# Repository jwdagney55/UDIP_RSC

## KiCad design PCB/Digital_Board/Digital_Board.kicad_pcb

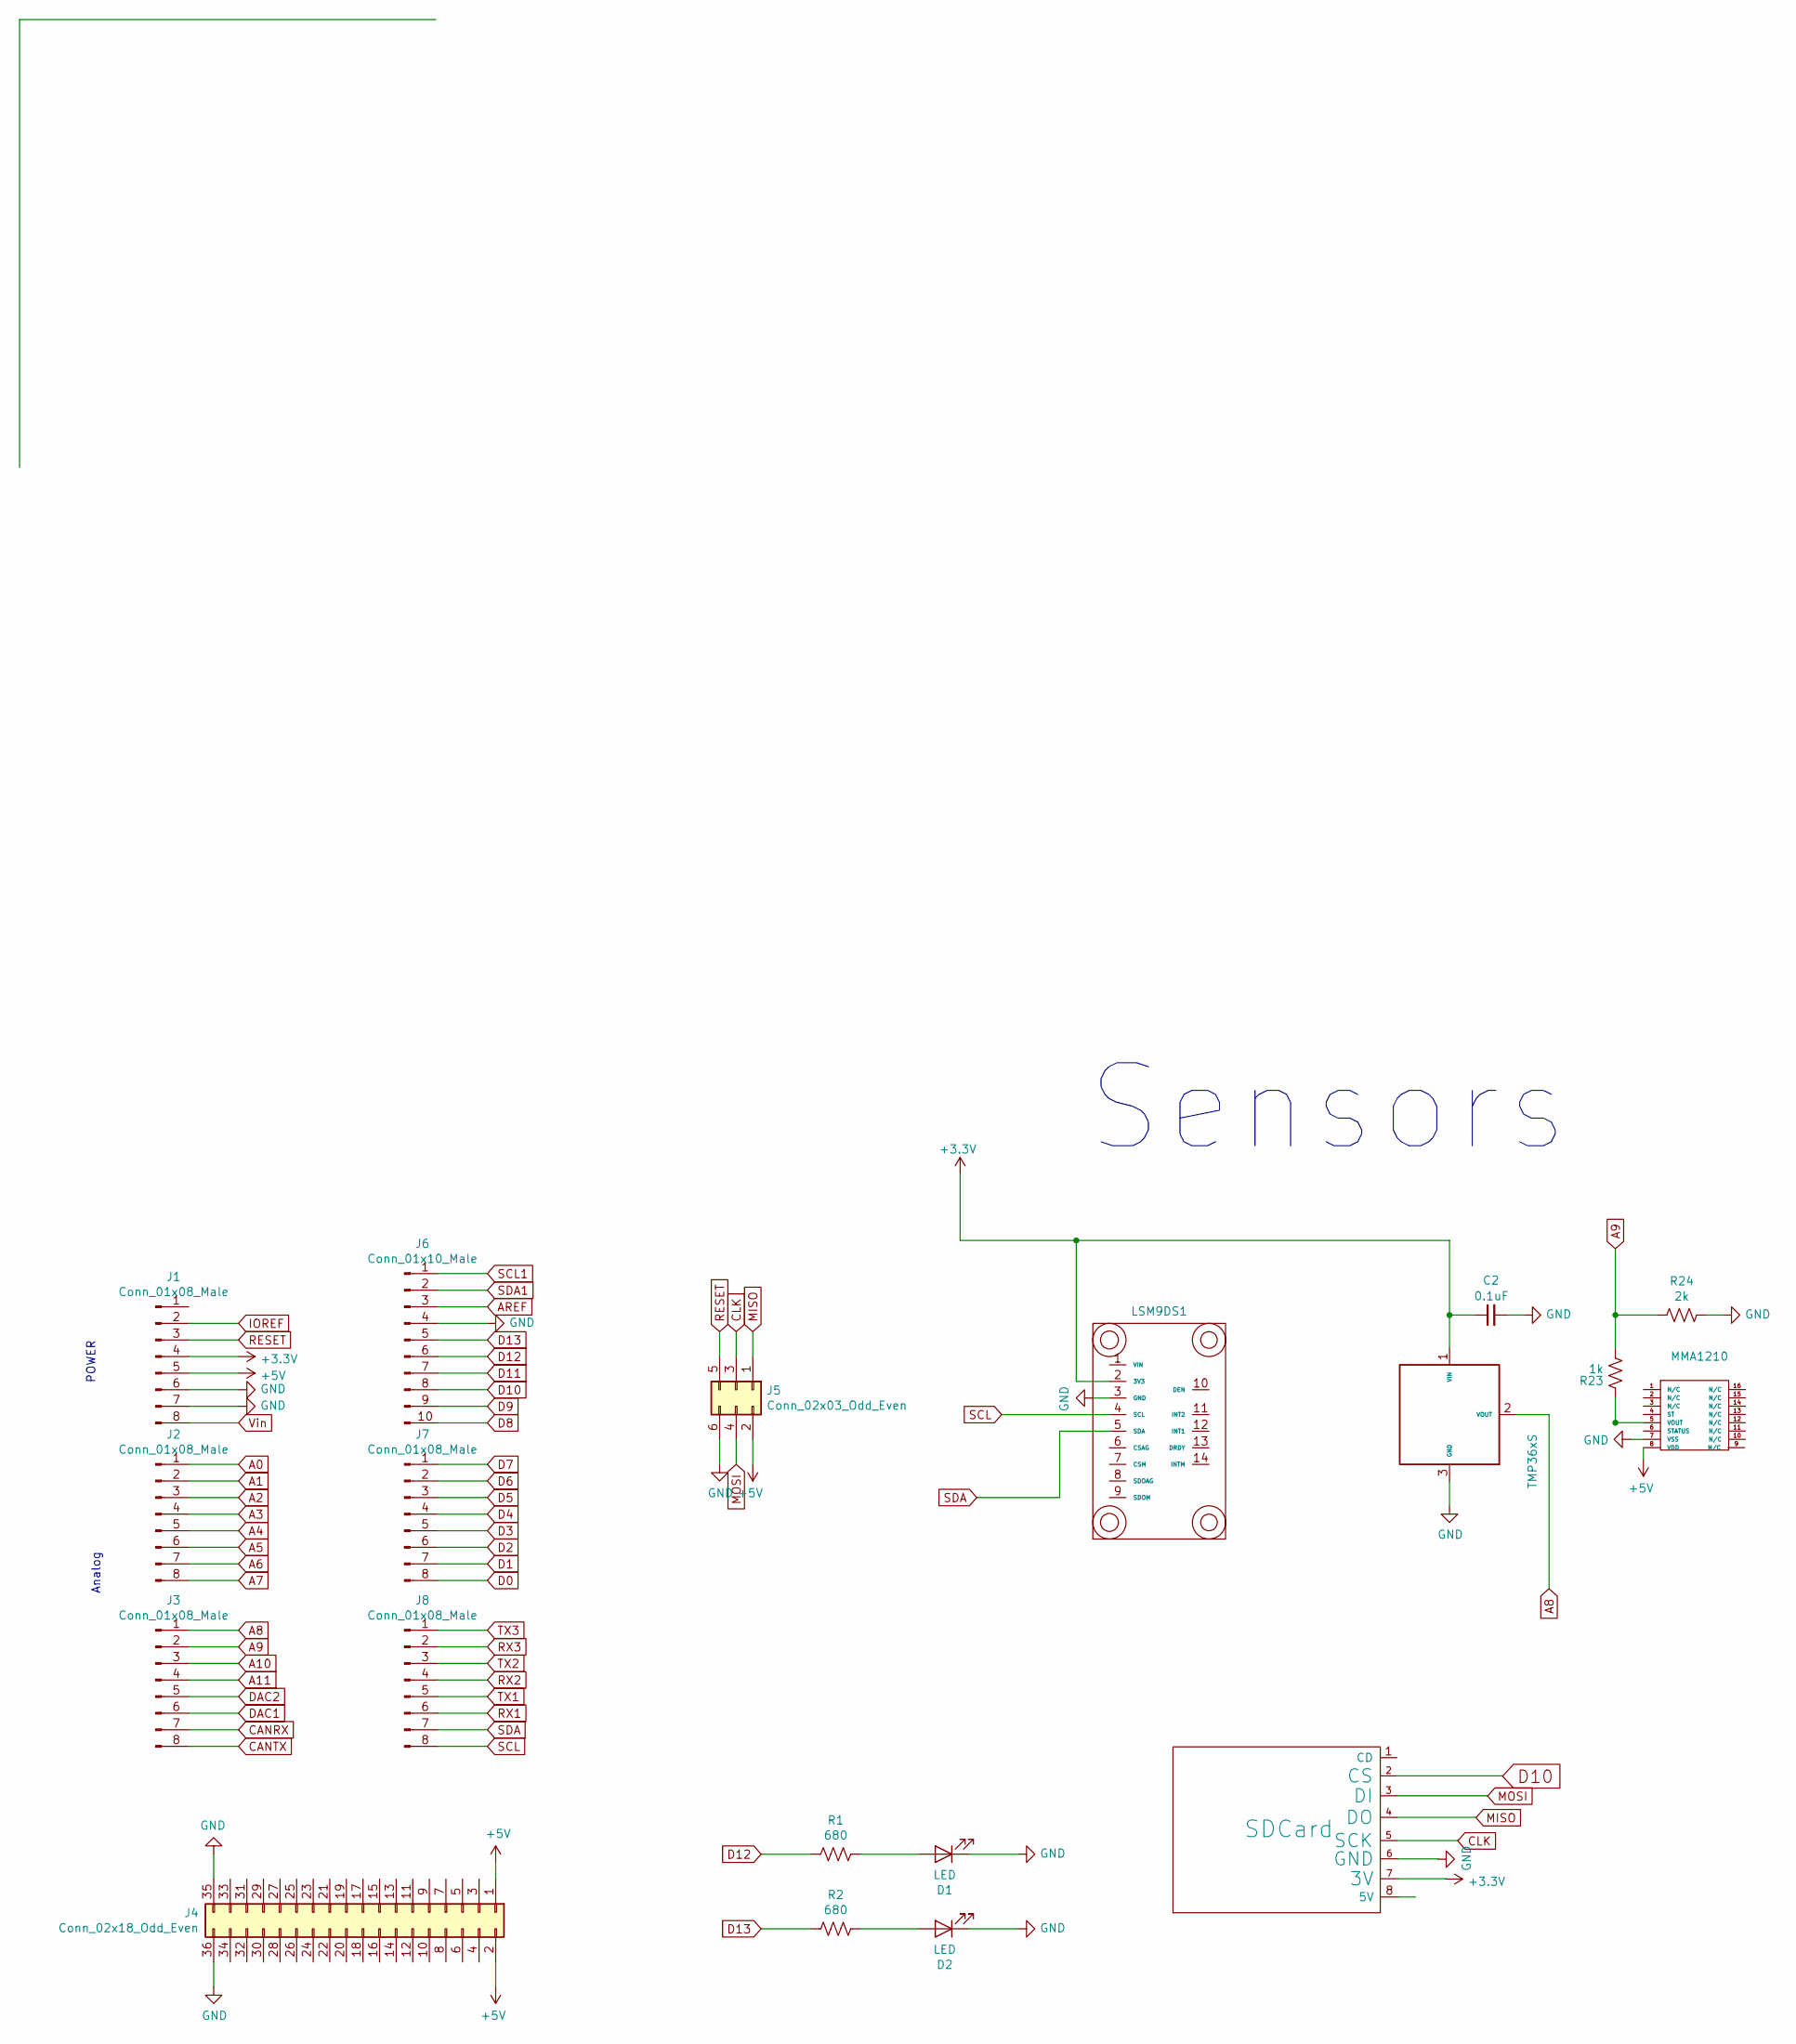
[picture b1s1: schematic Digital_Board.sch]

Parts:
C2: 0.1uF; C_0805_2012Metric_Pad1.15x1.40mm_HandSolder
D1, D2: LED; LED_1206_3216Metric
J1, J2, J3, J7, J8: Conn_01x08_Male; PinHeader_1x08_P2.54mm_Vertical
J4: Conn_02x18_Odd_Even; PinHeader_2x18_P2.54mm_Vertical
J5: Conn_02x03_Odd_Even; PinHeader_2x03_P2.54mm_Vertical
J6: Conn_01x10_Male; PinHeader_1x10_P2.54mm_Vertical
R1, R2: 680; R_0805_2012Metric_Pad1.15x1.40mm_HandSolder
R23: 1k; R_0805_2012Metric
R24: 2k; R_0805_2012Metric
U1: LSM9DS1; myLSM9DS1
U15: TMP36xS; PinHeader_1x03_P2.54mm_Vertical
U17: MMA1210
U18: SDCard; SD_CardV1

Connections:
+3V3: C2.1, J1.4, U1.2 (3V3), U15.1 (VIN), U18.7 (3V)
+5V: J1.5, J4.1, J4.2, J5.2, U17.8 (VDD)
A0: J2.1
A1: J2.2
A2: J2.3
A3: J2.4
A4: J2.5
A5: J2.6
A6: J2.7
A7: J2.8
A8: J3.1, U15.2 (VOUT)
A9: J3.2, R23.2, R24.2
A10: J3.3
A11: J3.4
AREF: J6.3
CANRX: J3.7
CANTX: J3.8
CLK: J5.3, U18.5 (SCK)
D0: J7.8
D1: J7.7
D2: J7.6
D3: J7.5
D4: J7.4
D5: J7.3
D6: J7.2
D7: J7.1
D8: J6.10
D9: J6.9
D10: J6.8, U18.2 (CS)
D11: J6.7
D12: J6.6, R1.2
D13: J6.5, R2.2
DAC1: J3.6
DAC2: J3.5
GND: C2.2, D1.1 (K), D2.1 (K), J1.6, J1.7, J4.35, J4.36, J5.6, J6.4, R24.1, U1.3 (GND), U15.3 (GND), U17.7 (VSS), U18.6 (GND)
IOREF: J1.2
MISO: J5.1, U18.4 (DO)
MOSI: J5.4, U18.3 (DI)
unnamed: D1.2 (A), R1.1
unnamed: D2.2 (A), R2.1
unnamed: R23.1, U17.5 (VOUT)
RESET: J1.3, J5.5
RX1: J8.6
RX2: J8.4
RX3: J8.2
SCL: J8.8, U1.4 (SCL)
SCL1: J6.1
SDA: J8.7, U1.5 (SDA)
SDA1: J6.2
TX1: J8.5
TX2: J8.3
TX3: J8.1
Vin: J1.8

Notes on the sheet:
POWER
Analog
Sensors

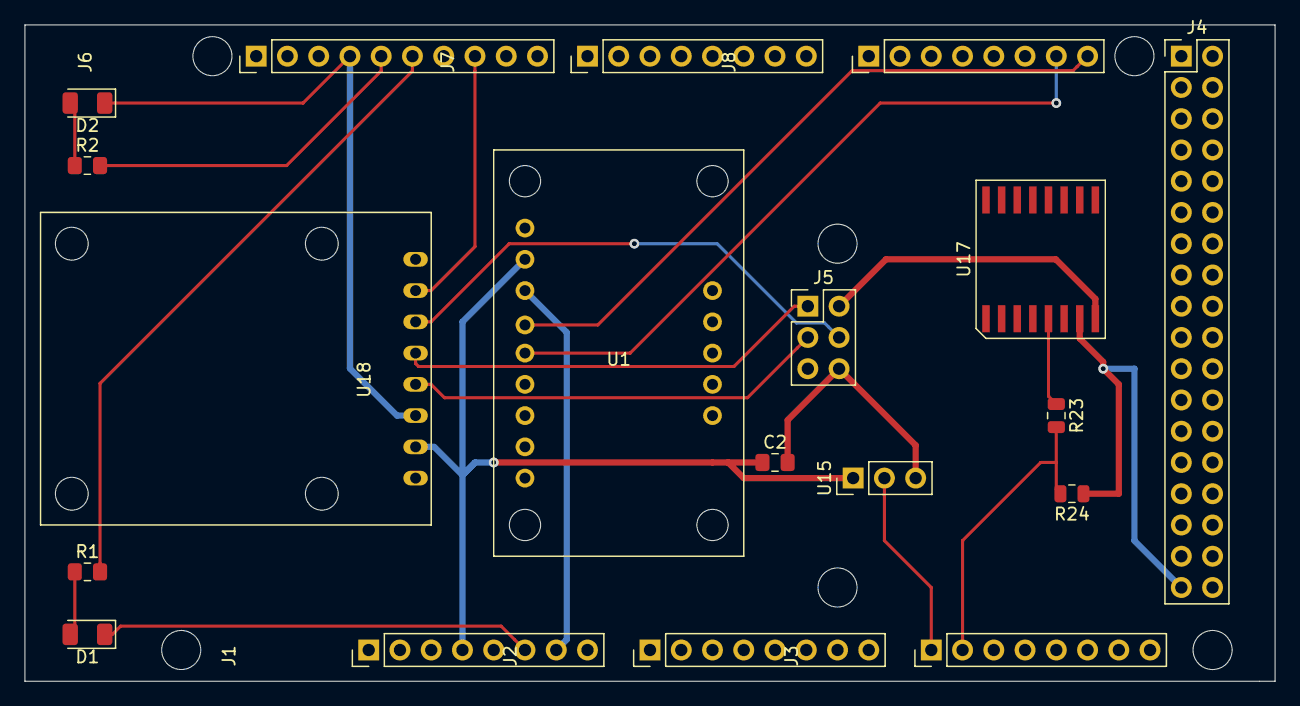
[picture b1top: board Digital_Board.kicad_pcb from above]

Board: 2 copper layers, 101.6 x 53.3 mm, 19 parts (0 on the bottom side), 17 nets.

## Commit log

2020-01-28 Digital PCB
2020-01-28 Digital PCB update
2020-02-01 Create Sweep Packet Software
2020-04-03 Update pythonScript.py
    Python Script
2020-04-03 Create UDIP_FSW.ino
    UDIP Flight Software w/ DAC arrays
2020-04-23 Update pythonScript.py
    Update sweep length
